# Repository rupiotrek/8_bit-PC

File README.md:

# 8_bit-PC

Project based on the project of [8 bit PC by Ben Eater](https://eater.net/8bit/ "8 bit by Ben Eater").  

# Version 1

Contains:
1. 3 board & schematic designs
2. Gerber files for production
3. BOM 

Board divided into 3 parts:

## Left

|Name of unit|Description|
| ------------ | ----------|
|**Clock**|Creats clock signal for the board. Can be used also as debugger - clock signal can be made by user |
|**Memory address (MAR)**|Choose from which address PC reads. In *Prog*  mode user can specify address to which instructions in RAM module will be written |
|**RAM**| Contains instructions for specified memory address. In *Prog* mode user can specify instruction for chosen in MAR module addres   |
|**Instruction register (IR)**| Decides which step of the program will be made next. It is sent to PC module. Also sends the address to read from  |
|**Control Word (CW)**| Operates whole PC. Also shows which flag is ON during working|

## Middle
|Name of unit|Description|
| ----- |-----|
|**Display module**|Shows current information on the bus   |
|**Sorting module**|Unit transports signals from left and right board to specified unit|

## Right
|Name of unit|Description|
|-----|-----|
|**Program counter (PC)**|Makes steps for the PC. Can also change them because of *jump* function    |
|**Power**| Main power unit. Contains overvoltage and reverse polarity protection |
|**A register**|Register that can read from and write informations for the bus. Contains information on which computer is working recently |
|**Arithmetic Logic Unit (ALU)**| Mathematical unit. Operates on variables from A and B registers. Module can add and substruct them   |
|**B register**|Register that can read informations from the bus. Contains information on which computer is working recently  |
|**Output register**| Show the variable on 4 display LED. Unit has two modes: non-neagtive and negative  |

# Links

This materials were really helpful during creation:

+ [Tutorial how to build the 8 bit PC](https://www.youtube.com/watch?v=HyznrdDSSGM&list=PLowKtXNTBypGqImE405J2565dvjafglHU)
+ [Ben Eater project site](https://eater.net/8bit/ )
+ [Helpful list of 74ls series ](https://www.futurlec.com/IC74LS00Series.shtml)

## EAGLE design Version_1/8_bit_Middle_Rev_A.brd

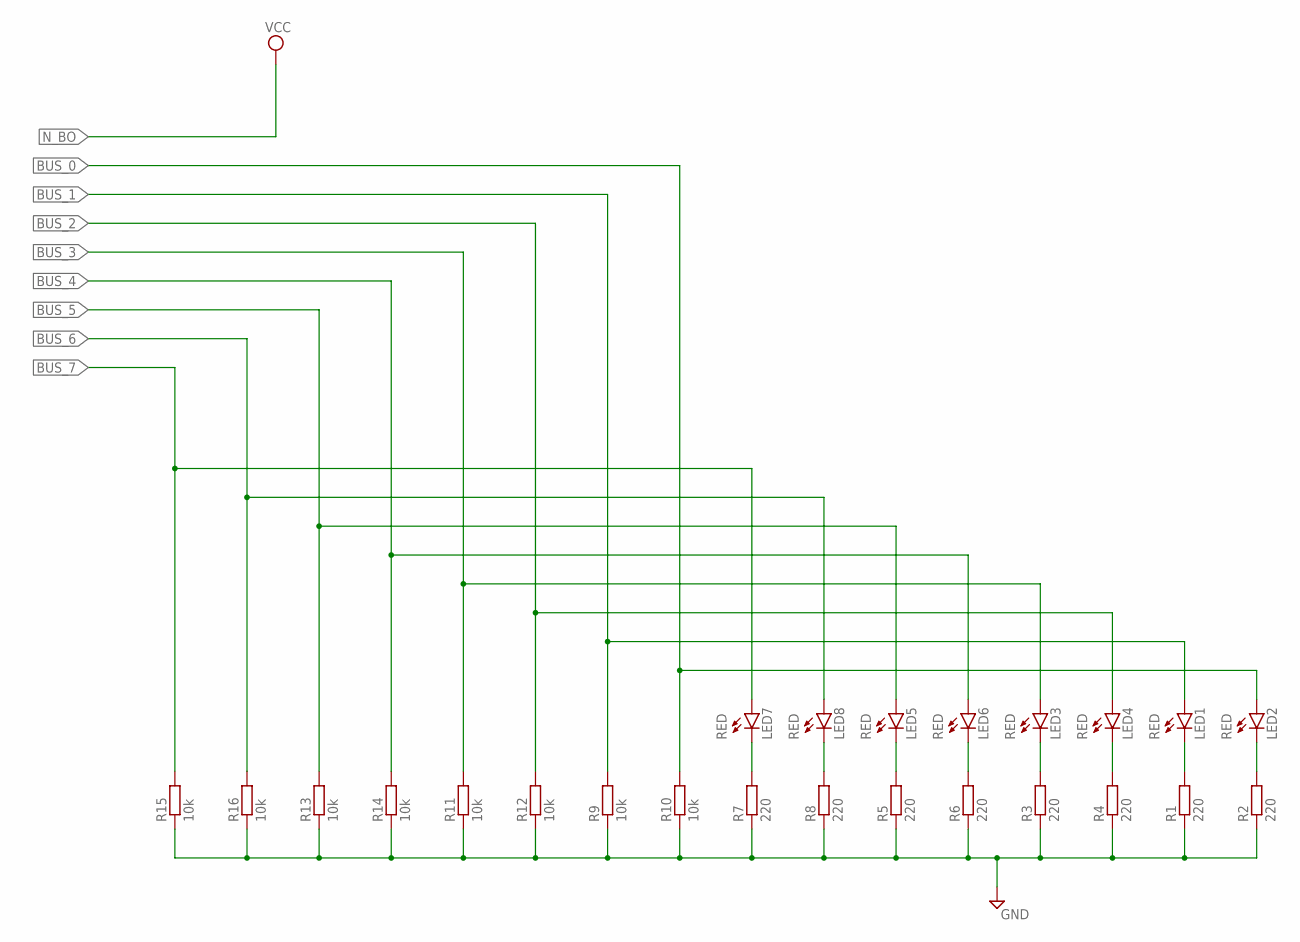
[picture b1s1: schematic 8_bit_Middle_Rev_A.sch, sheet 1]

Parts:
LED1, LED2, LED3, LED4, LED5, LED6, LED7, LED8: RED; LED5MM
R1, R2, R3, R4, R5, R6, R7, R8: 220; 0207/10
R9, R10, R11, R12, R13, R14, R15, R16: 10k; 0207/10

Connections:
BUS_0: LED2.A, R10.2; also elsewhere on the board
BUS_1: LED1.A, R9.2; also elsewhere on the board
BUS_2: LED4.A, R12.2; also elsewhere on the board
BUS_3: LED3.A, R11.2; also elsewhere on the board
BUS_4: LED6.A, R14.2; also elsewhere on the board
BUS_5: LED5.A, R13.2; also elsewhere on the board
BUS_6: LED8.A, R16.2; also elsewhere on the board
BUS_7: LED7.A, R15.2; also elsewhere on the board
GND: R1.1, R2.1, R3.1, R4.1, R5.1, R6.1, R7.1, R8.1, R9.1, R10.1, R11.1, R12.1, R13.1, R14.1, R15.1, R16.1; also elsewhere on the board
GND1: LED1.K (C), R1.2
GND2: LED2.K (C), R2.2
GND3: LED3.K (C), R3.2
GND5: LED4.K (C), R4.2
GND7: LED5.K (C), R5.2
GND8: LED6.K (C), R6.2
GND9: LED7.K (C), R7.2
GND10: LED8.K (C), R8.2

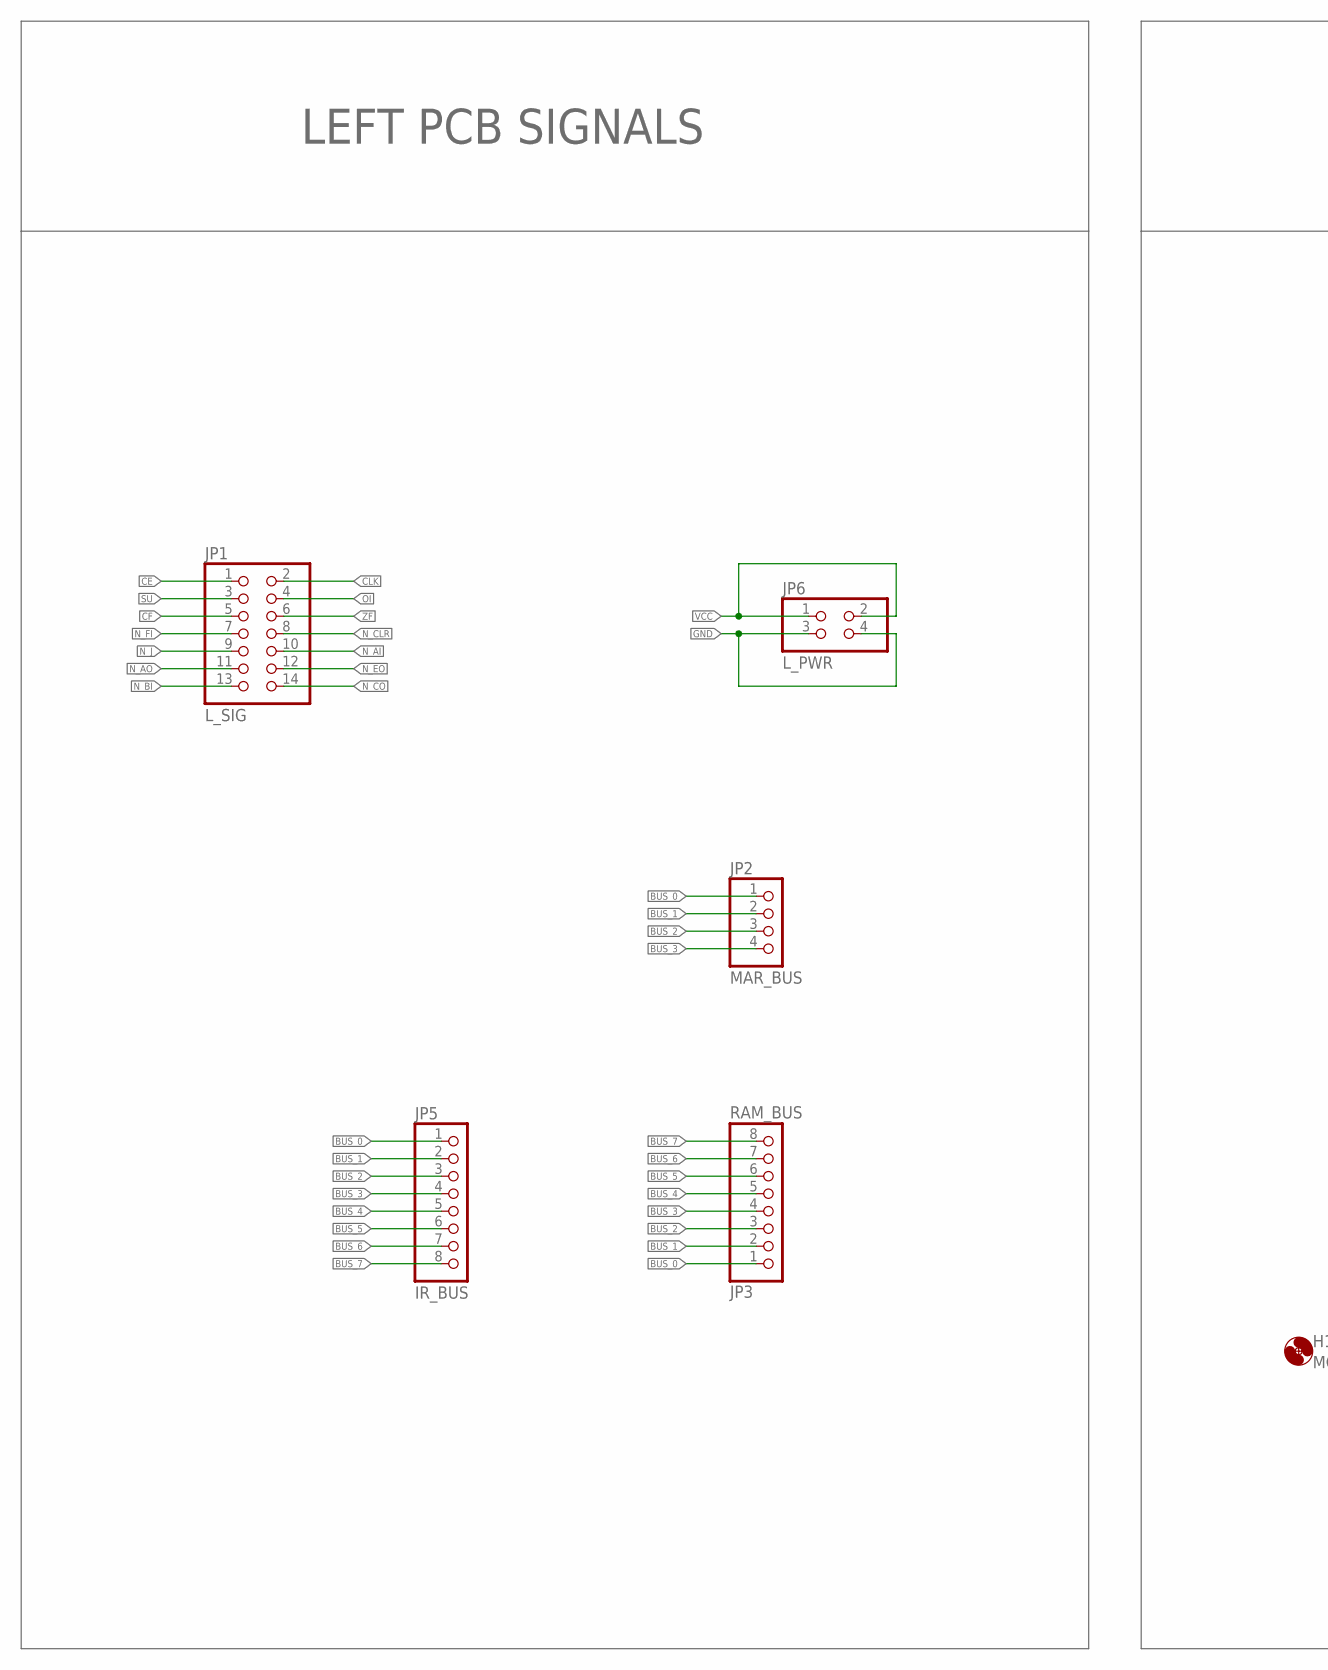
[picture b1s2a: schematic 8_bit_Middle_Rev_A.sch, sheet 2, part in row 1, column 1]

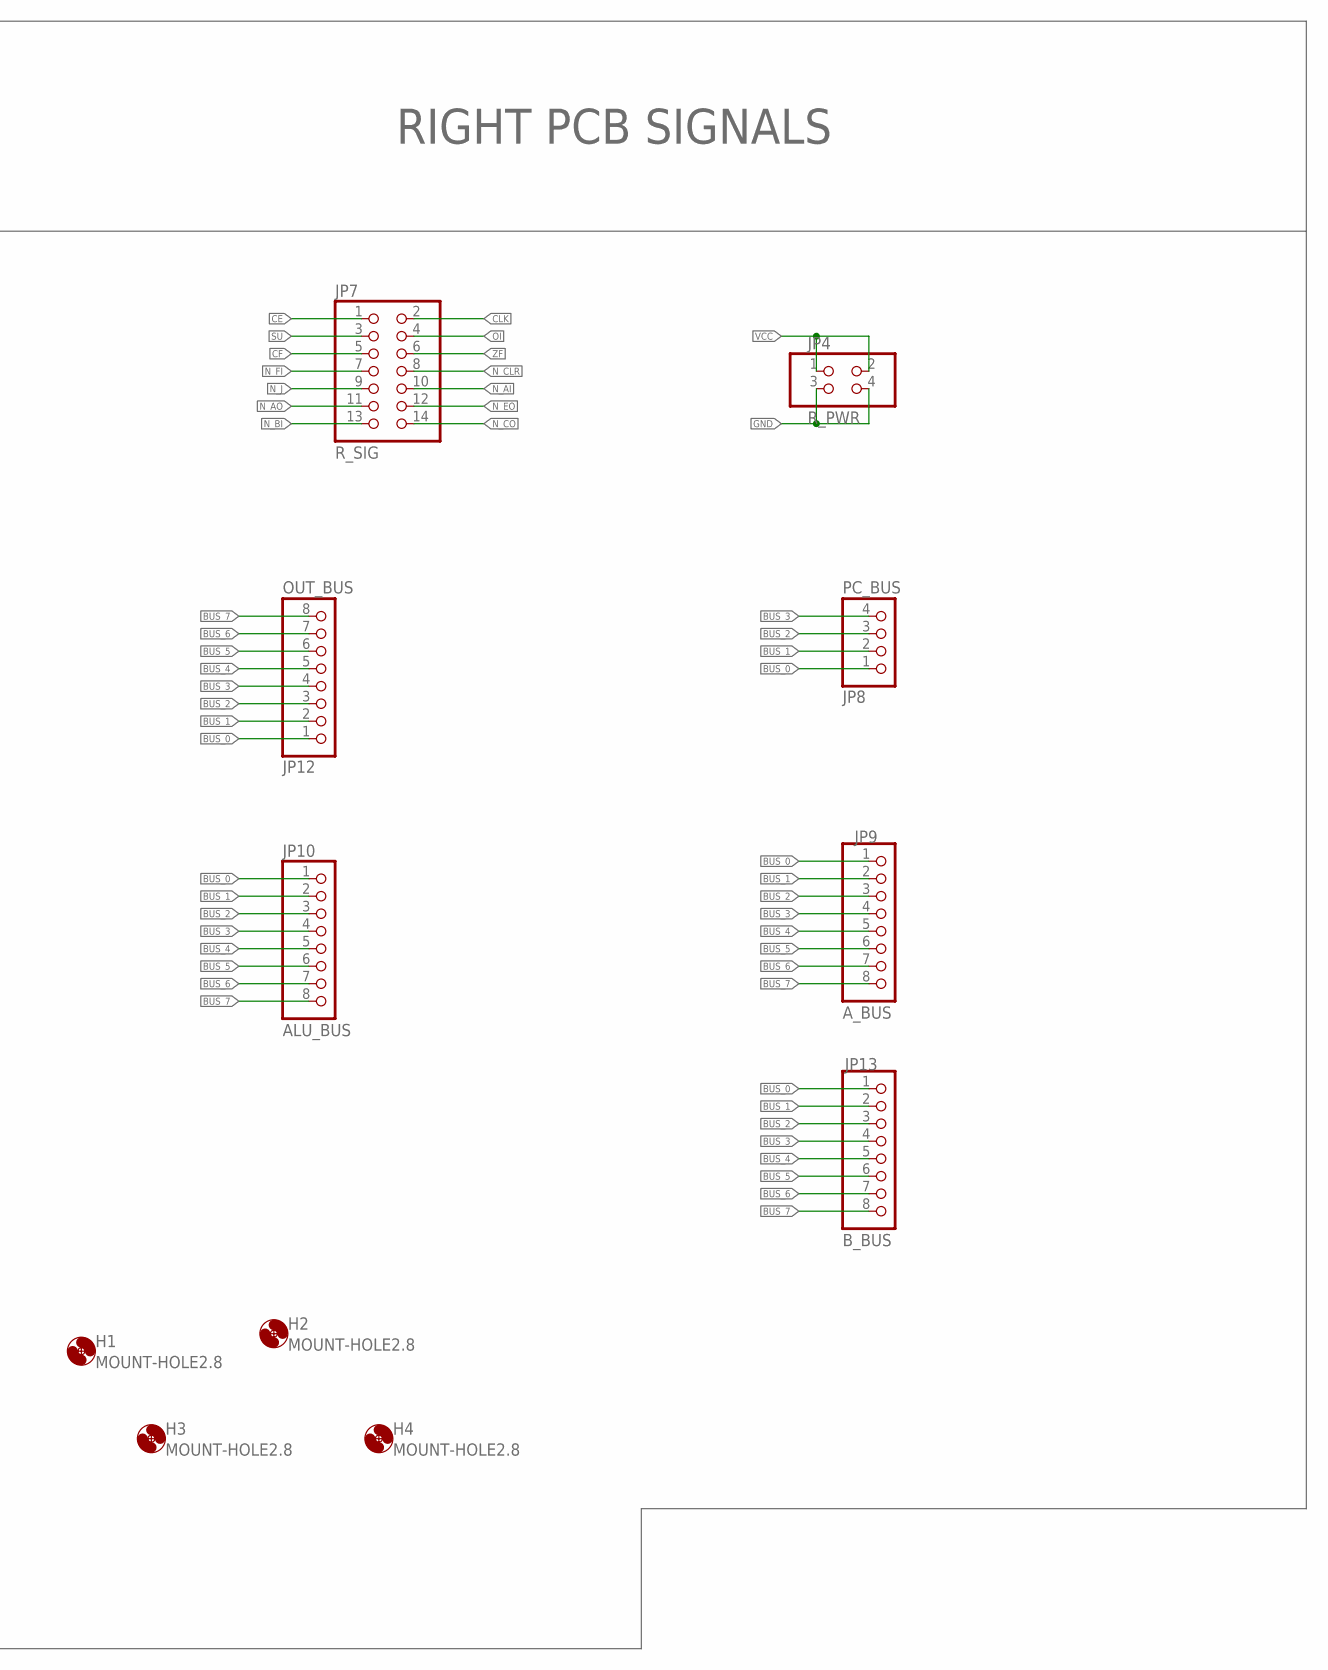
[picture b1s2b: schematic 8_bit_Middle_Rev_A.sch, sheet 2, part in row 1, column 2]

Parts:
H1, H2, H3, H4: MOUNT-HOLE2.8; 2,8
JP1: L_SIG; 2X07
JP2: MAR_BUS; 1X04
JP3: RAM_BUS; 1X08
JP4: R_PWR; 2X02
JP5: IR_BUS; 1X08
JP6: L_PWR; 2X02
JP7: R_SIG; 2X07
JP8: PC_BUS; 1X04
JP9: A_BUS; 1X08
JP10: ALU_BUS; 1X08
JP12: OUT_BUS; 1X08
JP13: B_BUS; 1X08

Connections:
BUS_0: JP2.1, JP3.1, JP5.1, JP8.1, JP9.1, JP10.1, JP12.1, JP13.1; also elsewhere on the board
BUS_1: JP2.2, JP3.2, JP5.2, JP8.2, JP9.2, JP10.2, JP12.2, JP13.2; also elsewhere on the board
BUS_2: JP2.3, JP3.3, JP5.3, JP8.3, JP9.3, JP10.3, JP12.3, JP13.3; also elsewhere on the board
BUS_3: JP2.4, JP3.4, JP5.4, JP8.4, JP9.4, JP10.4, JP12.4, JP13.4; also elsewhere on the board
BUS_4: JP3.5, JP5.5, JP9.5, JP10.5, JP12.5, JP13.5; also elsewhere on the board
BUS_5: JP3.6, JP5.6, JP9.6, JP10.6, JP12.6, JP13.6; also elsewhere on the board
BUS_6: JP3.7, JP5.7, JP9.7, JP10.7, JP12.7, JP13.7; also elsewhere on the board
BUS_7: JP3.8, JP5.8, JP9.8, JP10.8, JP12.8, JP13.8; also elsewhere on the board
CE: JP1.1, JP7.1
CF: JP1.5, JP7.5
CLK: JP1.2, JP7.2
GND: JP4.3, JP4.4, JP6.3, JP6.4; also elsewhere on the board
N_AI: JP1.10, JP7.10
N_AO: JP1.11, JP7.11
N_BI: JP1.13, JP7.13
N_CLR: JP1.8, JP7.8
N_CO: JP1.14, JP7.14
N_EO: JP1.12, JP7.12
N_FI: JP1.7, JP7.7
N_J: JP1.9, JP7.9
OI: JP1.4, JP7.4
SU: JP1.3, JP7.3
VCC: JP4.1, JP4.2, JP6.1, JP6.2
ZF: JP1.6, JP7.6

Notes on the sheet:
LEFT PCB SIGNALS
RIGHT PCB SIGNALS

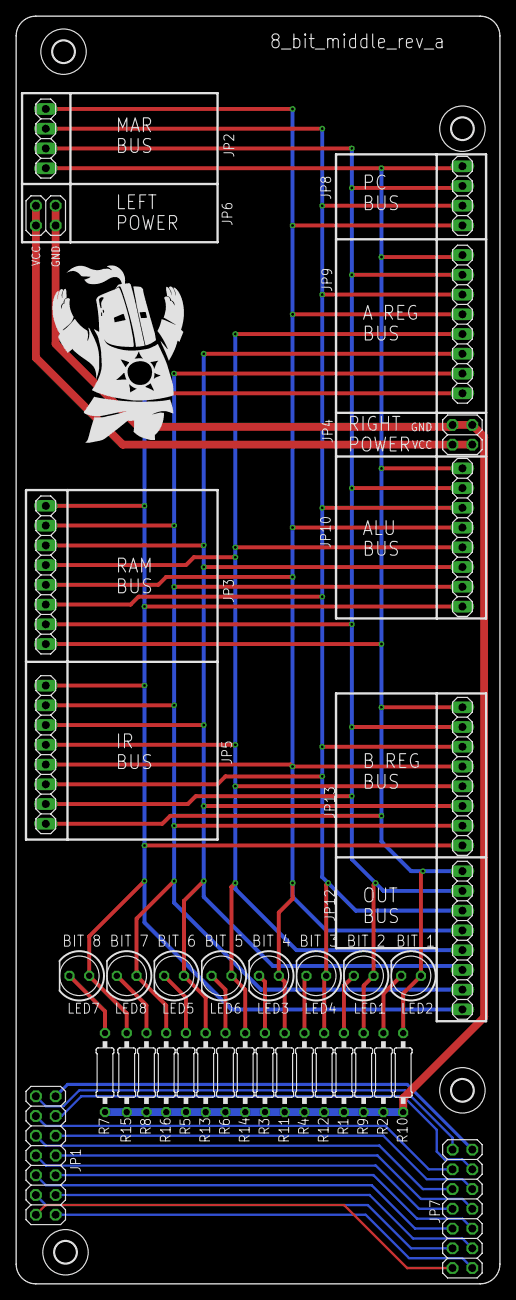
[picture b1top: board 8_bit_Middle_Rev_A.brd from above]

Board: 2 copper layers, 62.2 x 163.1 mm, 42 parts (1 on the bottom side), 32 nets.

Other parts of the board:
U$1: SOLAIRE
U$2: MUELLTONNE

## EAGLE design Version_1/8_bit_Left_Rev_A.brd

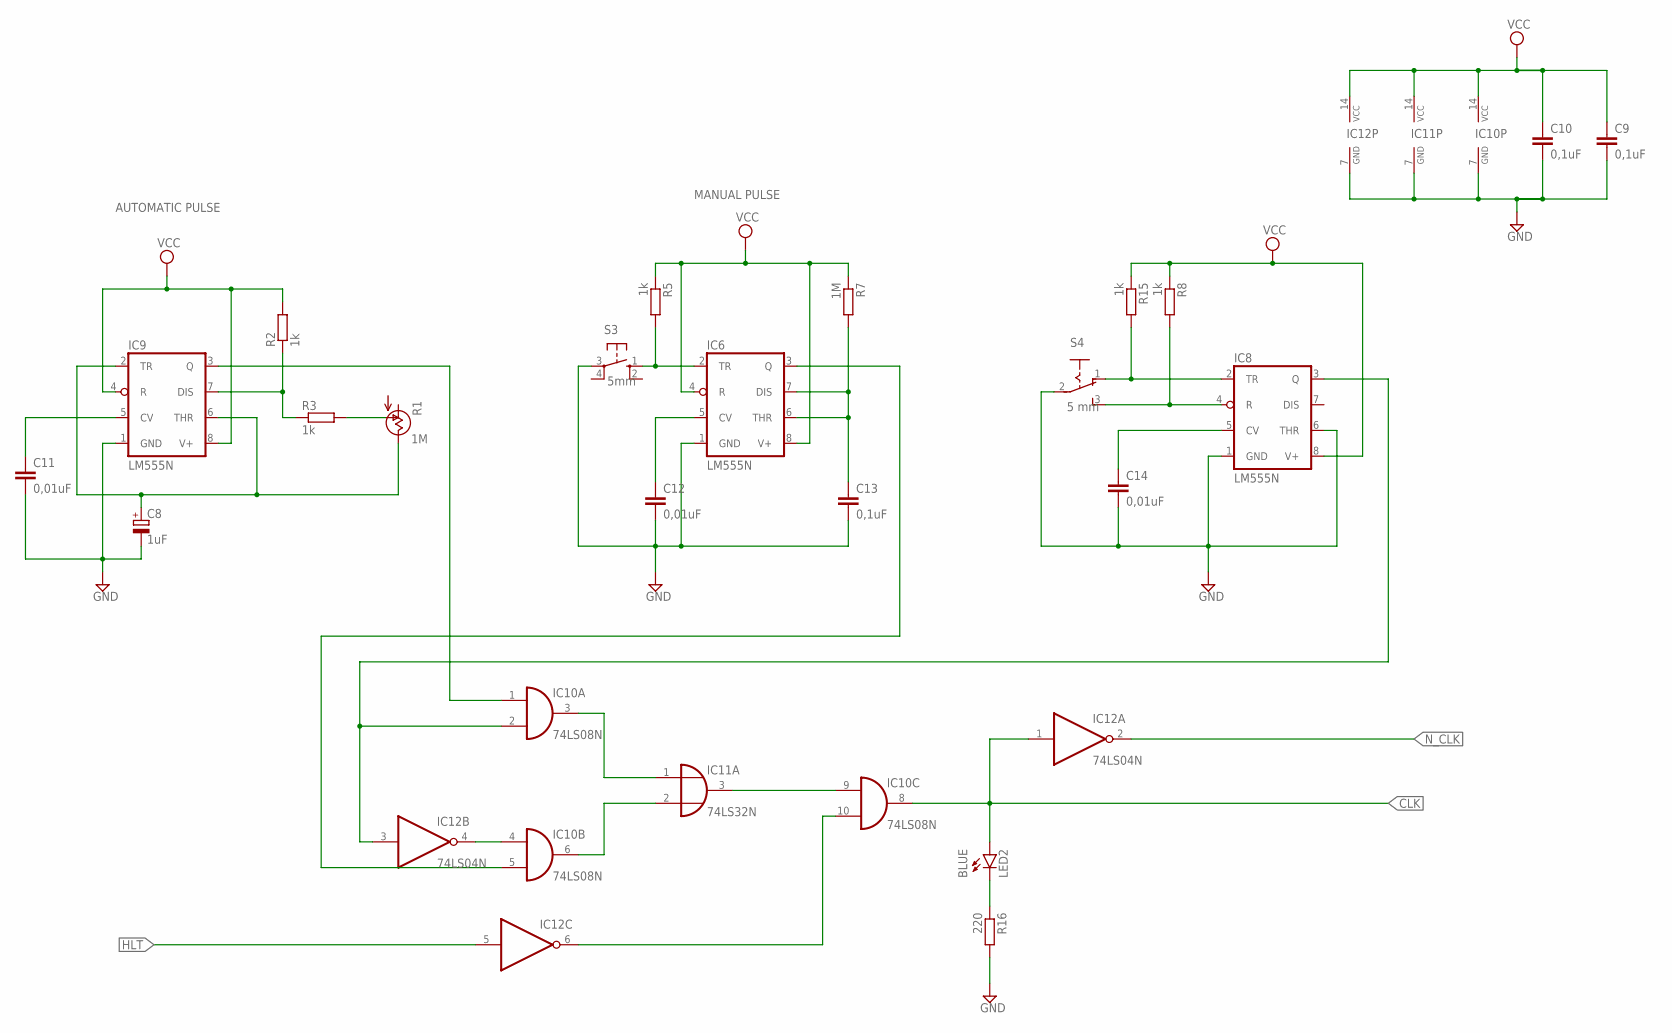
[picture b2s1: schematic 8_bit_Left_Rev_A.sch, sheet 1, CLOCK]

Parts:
C8: 1uF; E2-5
C9, C10, C13: 0,1uF; C025-030X050
C11, C12, C14: 0,01uF; C025-030X050
IC6, IC8, IC9: LM555N; DIL08
IC10: 74LS08N; DIL14
IC11: 74LS32N; DIL14
IC12: 74LS04N; DIL14
LED2: BLUE; LED5MM
R1: 1M; S64W
R2, R3, R5, R8, R15: 1k; 0207/10
R7: 1M; 0207/10
R16: 220; 0207/10
S3: 5mm; B3F-10XX
S4: 5 mm; 255SB

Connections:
CLK: IC10.8 (O), IC12.1 (I), LED2.A; also elsewhere on the board
GND: C8.-, C9.2, C10.2, C11.2, C12.2, C13.2, C14.2, IC6.1 (GND), IC8.1 (GND), IC8.6 (THR), IC9.1 (GND), IC10.7 (GND), IC11.7 (GND), IC12.7 (GND), R16.2, S3.3, S4.2; also elsewhere on the board
HLT: IC12.5 (I); also elsewhere on the board
unnamed: IC9.7 (DIS), R2.1, R3.1
unnamed: C8.+, IC9.2 (TR), IC9.6 (THR), R1.E (VSS)
unnamed: C11.1, IC9.5 (CV)
unnamed: C12.1, IC6.5 (CV)
unnamed: C13.1, IC6.6 (THR), IC6.7 (DIS), R7.2
unnamed: IC6.2 (TR), R5.2, S3.1 (S)
unnamed: IC8.4 (R), R8.2, S4.3 (S)
unnamed: IC8.2 (TR), R15.2, S4.1 (O)
unnamed: C14.1, IC8.5 (CV)
unnamed: IC9.3 (Q), IC10.1 (I0)
unnamed: IC6.3 (Q), IC10.5 (I1)
unnamed: IC10.4 (I0), IC12.4 (O)
unnamed: IC8.3 (Q), IC10.2 (I1), IC12.3 (I)
unnamed: IC10.3 (O), IC11.1 (I0)
unnamed: IC10.6 (O), IC11.2 (I1)
unnamed: IC10.9 (I0), IC11.3 (O)
unnamed: IC10.10 (I1), IC12.6 (O)
unnamed: R1.S (OUT), R3.2
unnamed: LED2.K (C), R16.1
N_CLK: IC12.2 (O); also elsewhere on the board
VCC: C9.1, C10.1, IC6.4 (R), IC6.8 (V+), IC8.8 (V+), IC9.4 (R), IC9.8 (V+), IC10.14 (VCC), IC11.14 (VCC), IC12.14 (VCC), R2.2, R5.1, R7.1, R8.1, R15.1; also elsewhere on the board

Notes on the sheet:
MANUAL PULSE
AUTOMATIC PULSE

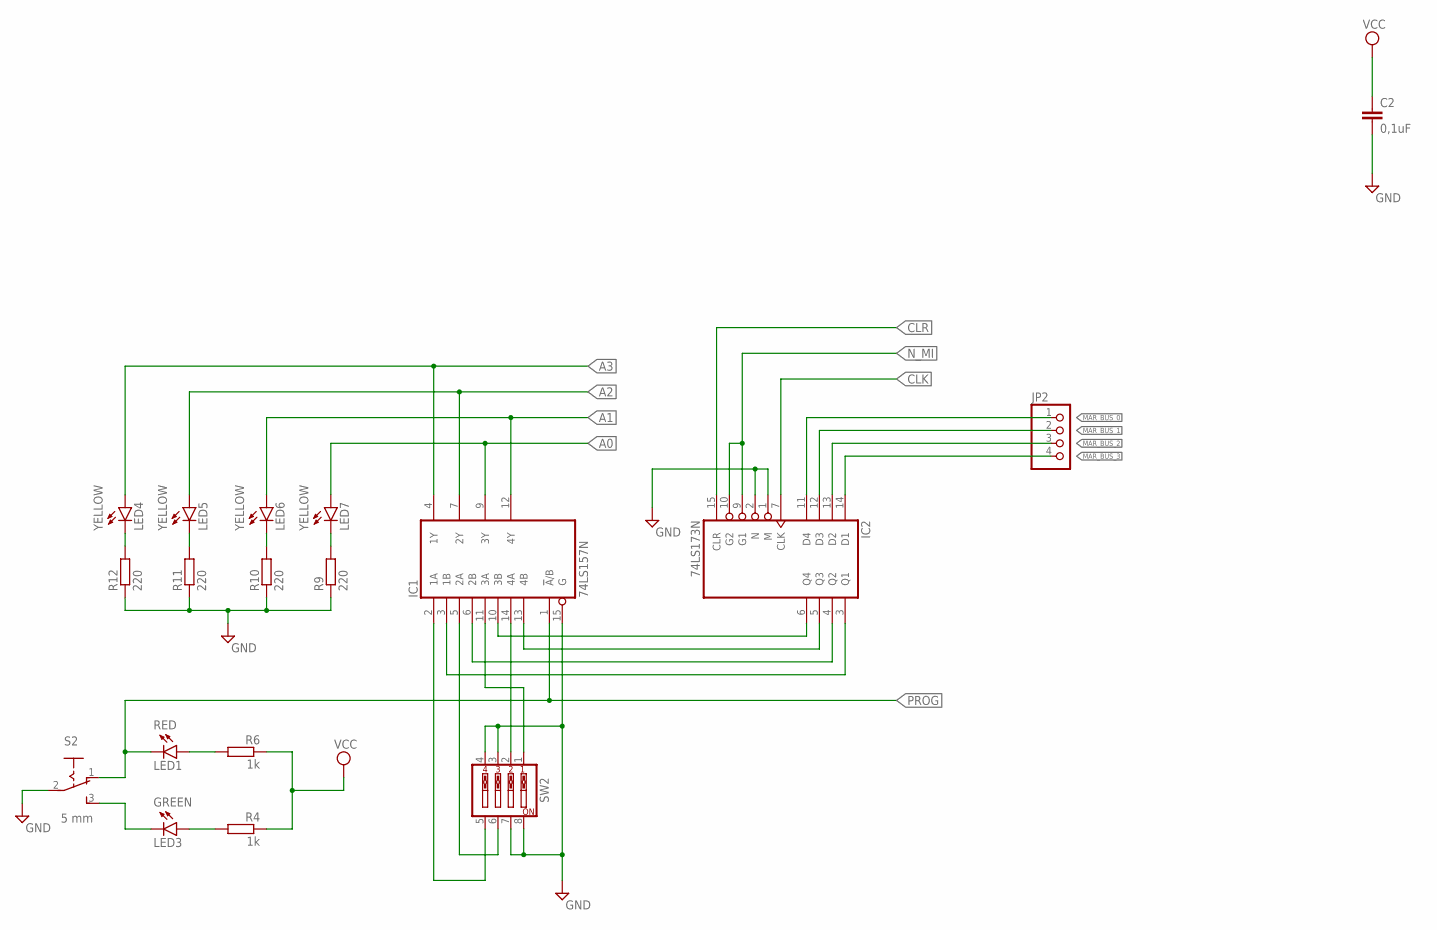
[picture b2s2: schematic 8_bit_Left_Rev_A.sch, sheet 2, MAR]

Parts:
C2: 0,1uF; C025-030X050
IC1: 74LS157N; DIL16
IC2: 74LS173N; DIL16
JP2: PINHD-1X4; 1X04
LED1: RED; LED5MM
LED3: GREEN; LED5MM
LED4, LED5, LED6, LED7: YELLOW; LED5MM
R4, R6: 1k; 0207/10
R9, R10, R11, R12: 220; 0207/10
S2: 5 mm; 255SB
SW2: EDG-04

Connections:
A0: IC1.9 (3Y), LED7.A; also elsewhere on the board
A1: IC1.12 (4Y), LED6.A; also elsewhere on the board
A2: IC1.7 (2Y), LED5.A; also elsewhere on the board
A3: IC1.4 (1Y), LED4.A; also elsewhere on the board
CLK: IC2.7 (CLK); also elsewhere on the board
CLR: IC2.15 (CLR); also elsewhere on the board
GND: C2.2, IC1.8 (GND), IC1.15 (G), IC2.1 (M), IC2.2 (N), IC2.8 (GND), R9.1, R10.1, R11.1, R12.1, S2.2, SW2.3, SW2.4, SW2.7, SW2.8; also elsewhere on the board
GND1: LED7.K (C), R9.2
GND2: LED6.K (C), R10.2
GND3: LED5.K (C), R11.2
GND4: LED4.K (C), R12.2
MAR_BUS_0: IC2.11 (D4), JP2.1
MAR_BUS_1: IC2.12 (D3), JP2.2
MAR_BUS_2: IC2.13 (D2), JP2.3
MAR_BUS_3: IC2.14 (D1), JP2.4
unnamed: LED1.A, R6.2
unnamed: LED3.A, R4.2
unnamed: LED3.K (C), S2.3 (S)
unnamed: IC1.14 (4A), SW2.2
unnamed: IC1.11 (3A), SW2.1
unnamed: IC1.10 (3B), IC2.6 (Q4)
unnamed: IC1.13 (4B), IC2.5 (Q3)
unnamed: IC1.6 (2B), IC2.4 (Q2)
unnamed: IC1.3 (1B), IC2.3 (Q1)
unnamed: IC1.5 (2A), SW2.6
unnamed: IC1.2 (1A), SW2.5
N_MI: IC2.9 (G1), IC2.10 (G2); also elsewhere on the board
PROG: IC1.1 (!A!/B), LED1.K (C), S2.1 (O); also elsewhere on the board
VCC: C2.1, IC1.16 (VCC), IC2.16 (VCC), R4.1, R6.1; also elsewhere on the board

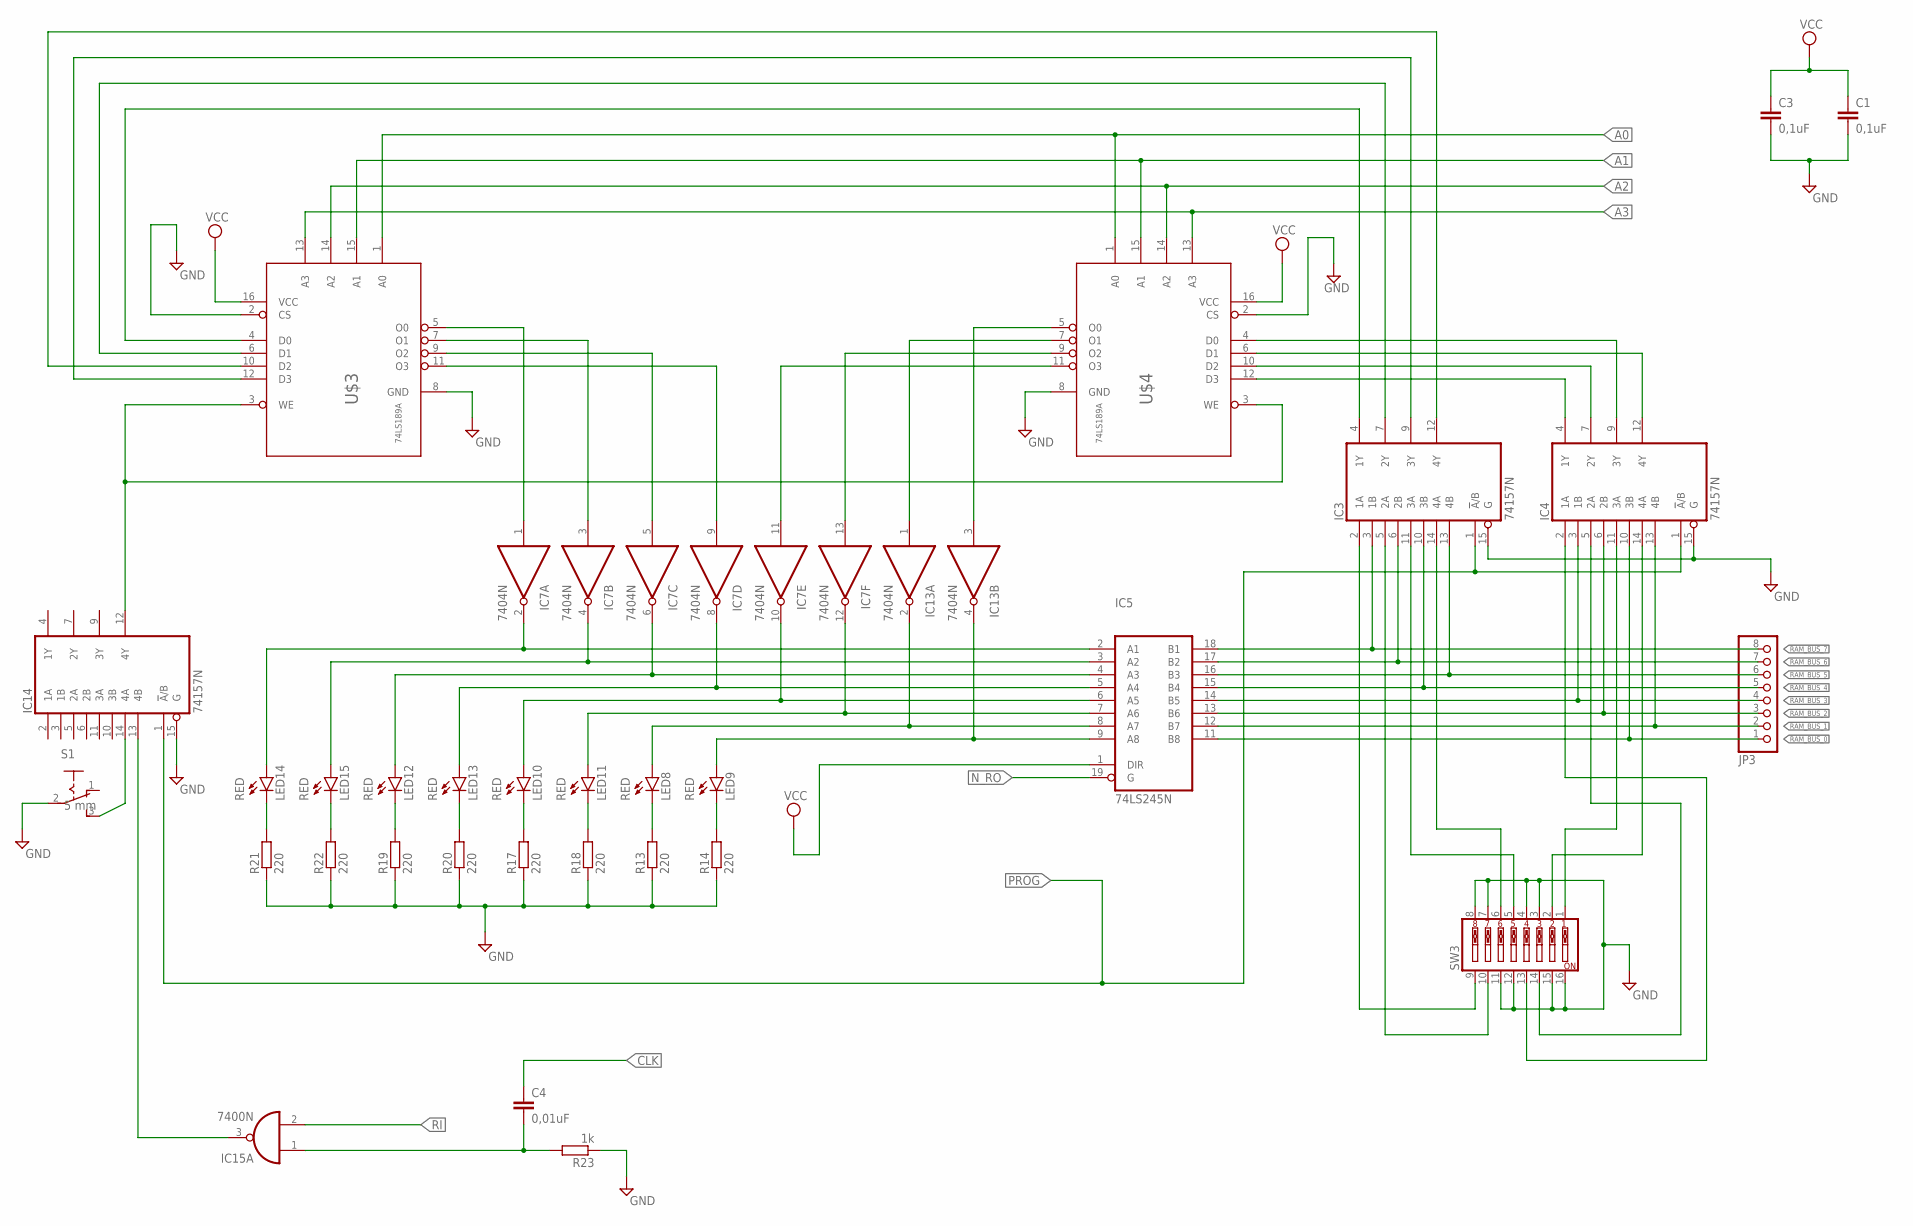
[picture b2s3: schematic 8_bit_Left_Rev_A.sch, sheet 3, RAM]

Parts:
C1, C3: 0,1uF; C025-030X050
C4: 0,01uF; C025-030X050
IC3, IC4, IC14: 74157N; DIL16
IC5: 74LS245N; DIL20
IC7, IC13: 7404N; DIL14
IC15: 7400N; DIL14
JP3: PINHD-1X8; 1X08
LED8, LED9, LED10, LED11, LED12, LED13, LED14, LED15: RED; LED5MM
R13, R14, R17, R18, R19, R20, R21, R22: 220; 0207/10
R23: 1k; 0207/10
S1: 5 mm; 255SB
SW3: EDG-08
U$3, U$4: 74LS189A; 74LS189

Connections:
A0: U$3.1 (A0), U$4.1 (A0); also elsewhere on the board
A1: U$3.15 (A1), U$4.15 (A1); also elsewhere on the board
A2: U$3.14 (A2), U$4.14 (A2); also elsewhere on the board
A3: U$3.13 (A3), U$4.13 (A3); also elsewhere on the board
CLK: C4.1; also elsewhere on the board
GND: C1.2, C3.2, IC3.8 (GND), IC3.15 (G), IC4.8 (GND), IC4.15 (G), IC5.10 (GND), IC7.7 (GND), IC13.7 (GND), IC14.8 (GND), IC14.15 (G), IC15.7 (GND), R13.1, R14.1, R17.1, R18.1, R19.1, R20.1, R21.1, R22.1, R23.1, S1.2, SW3.3, SW3.4, SW3.7, SW3.8, SW3.11, SW3.12, SW3.15, SW3.16, U$3.2 (CS), U$3.8 (GND), U$4.2 (CS), U$4.8 (GND); also elsewhere on the board
GND5: LED8.K (C), R13.2
GND6: LED9.K (C), R14.2
GND7: LED10.K (C), R17.2
GND8: LED11.K (C), R18.2
GND9: LED12.K (C), R19.2
GND10: LED13.K (C), R20.2
GND11: LED14.K (C), R21.2
GND12: LED15.K (C), R22.2
unnamed: IC3.4 (1Y), U$3.4 (D0)
unnamed: IC3.7 (2Y), U$3.6 (D1)
unnamed: IC3.9 (3Y), U$3.12 (D3)
unnamed: IC3.12 (4Y), U$3.10 (D2)
unnamed: IC14.12 (4Y), U$3.3 (WE), U$4.3 (WE)
unnamed: IC13.3 (I), U$4.5 (O0)
unnamed: IC13.1 (I), U$4.7 (O1)
unnamed: IC7.13 (I), U$4.9 (O2)
unnamed: IC7.11 (I), U$4.11 (O3)
unnamed: IC7.1 (I), U$3.5 (O0)
unnamed: IC7.3 (I), U$3.7 (O1)
unnamed: IC7.5 (I), U$3.9 (O2)
unnamed: IC7.9 (I), U$3.11 (O3)
unnamed: IC5.2 (A1), IC7.2 (O), LED14.A
unnamed: IC5.3 (A2), IC7.4 (O), LED15.A
unnamed: IC5.4 (A3), IC7.6 (O), LED12.A
unnamed: IC5.5 (A4), IC7.8 (O), LED13.A
unnamed: IC5.6 (A5), IC7.10 (O), LED10.A
unnamed: IC5.7 (A6), IC7.12 (O), LED11.A
unnamed: IC5.8 (A7), IC13.2 (O), LED8.A
unnamed: IC5.9 (A8), IC13.4 (O), LED9.A
unnamed: IC14.14 (4A), S1.3 (S)
unnamed: IC14.13 (4B), IC15.3 (O)
unnamed: C4.2, IC15.1 (I0), R23.2
unnamed: IC3.2 (1A), SW3.9
unnamed: IC3.5 (2A), SW3.10
unnamed: IC3.11 (3A), SW3.5
unnamed: IC3.14 (4A), SW3.6
unnamed: IC4.14 (4A), SW3.2
unnamed: IC4.5 (2A), SW3.14
unnamed: IC4.11 (3A), SW3.1
unnamed: IC4.2 (1A), SW3.13
unnamed: IC4.9 (3Y), U$4.4 (D0)
unnamed: IC4.4 (1Y), U$4.12 (D3)
unnamed: IC4.7 (2Y), U$4.10 (D2)
unnamed: IC4.12 (4Y), U$4.6 (D1)
N_RO: IC5.19 (G); also elsewhere on the board
PROG: IC3.1 (!A!/B), IC4.1 (!A!/B), IC14.1 (!A!/B); also elsewhere on the board
RAM_BUS_0: IC4.10 (3B), IC5.11 (B8), JP3.1
RAM_BUS_1: IC4.13 (4B), IC5.12 (B7), JP3.2
RAM_BUS_2: IC4.6 (2B), IC5.13 (B6), JP3.3
RAM_BUS_3: IC4.3 (1B), IC5.14 (B5), JP3.4
RAM_BUS_4: IC3.10 (3B), IC5.15 (B4), JP3.5
RAM_BUS_5: IC3.13 (4B), IC5.16 (B3), JP3.6
RAM_BUS_6: IC3.6 (2B), IC5.17 (B2), JP3.7
RAM_BUS_7: IC3.3 (1B), IC5.18 (B1), JP3.8
RI: IC15.2 (I1); also elsewhere on the board
VCC: C1.1, C3.1, IC3.16 (VCC), IC4.16 (VCC), IC5.1 (DIR), IC5.20 (VCC), IC7.14 (VCC), IC13.14 (VCC), IC14.16 (VCC), IC15.14 (VCC), U$3.16 (VCC), U$4.16 (VCC); also elsewhere on the board

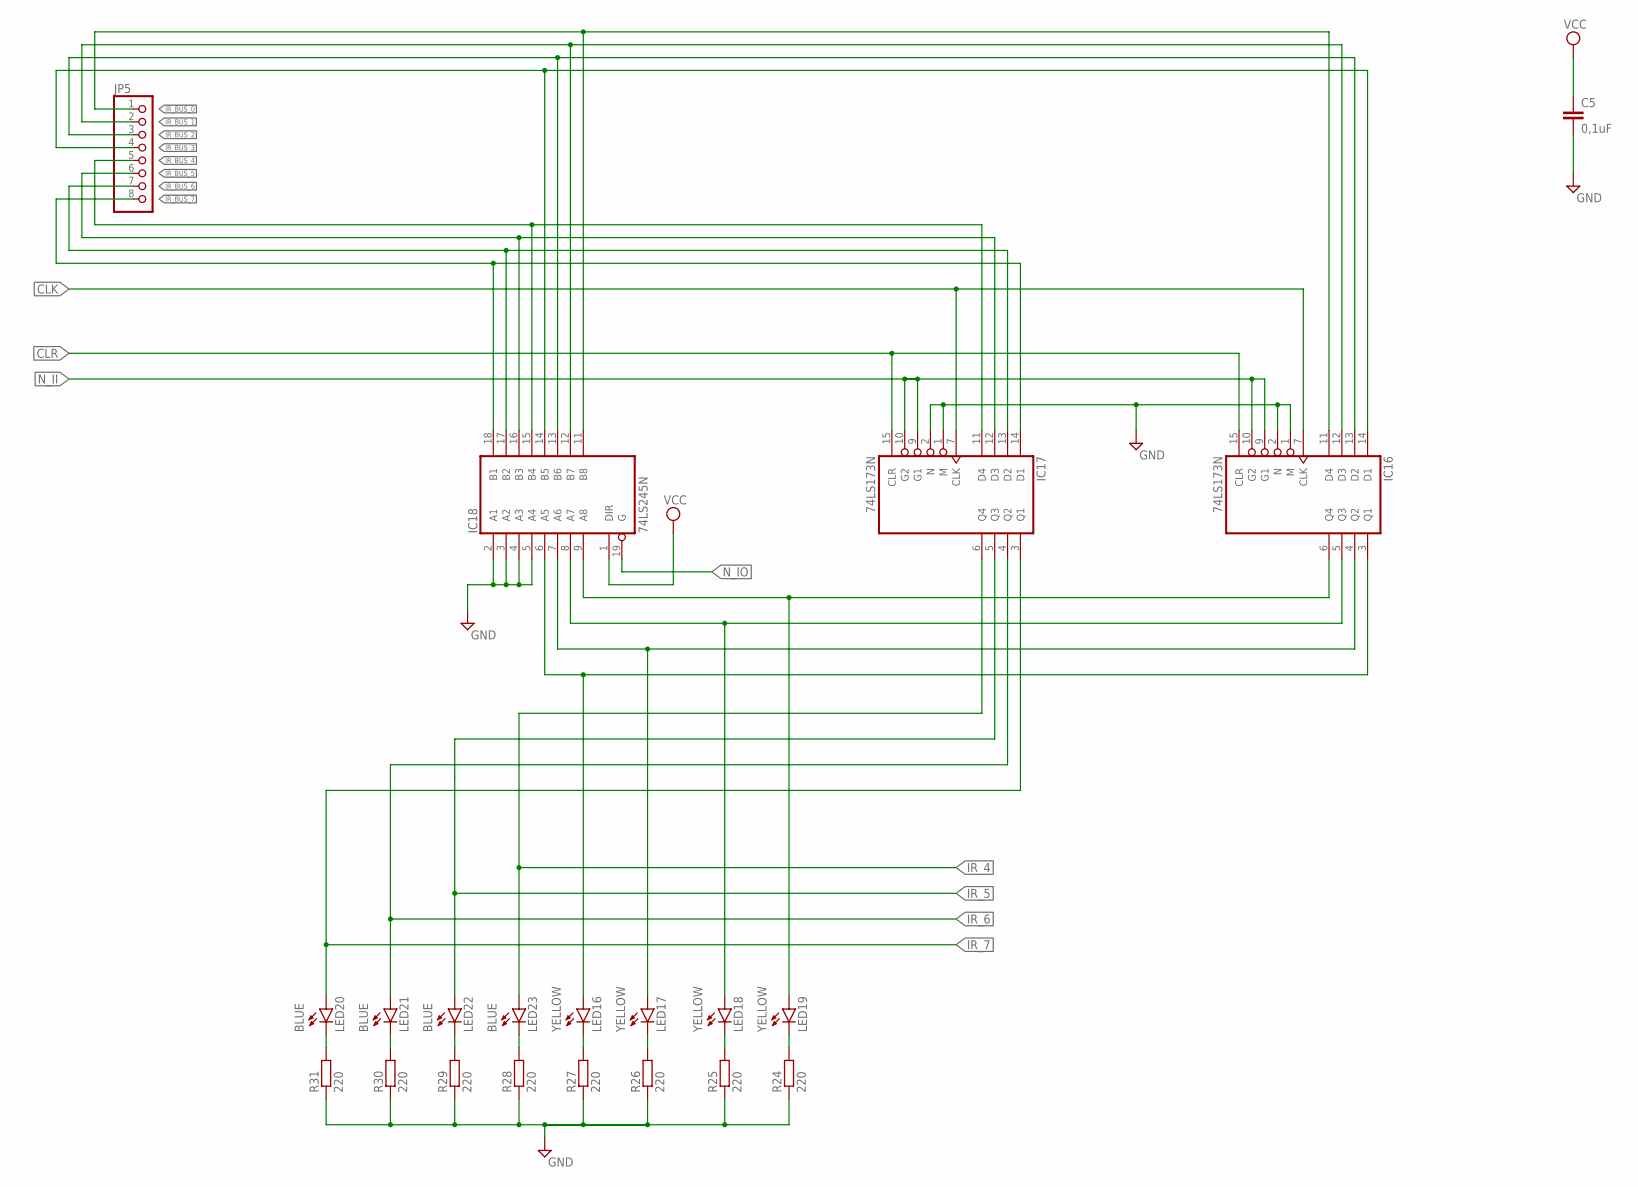
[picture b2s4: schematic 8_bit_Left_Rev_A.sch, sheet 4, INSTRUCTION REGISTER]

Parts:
C5: 0,1uF; C025-030X050
IC16, IC17: 74LS173N; DIL16
IC18: 74LS245N; DIL20
JP5: PINHD-1X8; 1X08
LED16, LED17, LED18, LED19: YELLOW; LED5MM
LED20, LED21, LED22, LED23: BLUE; LED5MM
R24, R25, R26, R27, R28, R29, R30, R31: 220; 0207/10

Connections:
CLK: IC16.7 (CLK), IC17.7 (CLK); also elsewhere on the board
CLR: IC16.15 (CLR), IC17.15 (CLR); also elsewhere on the board
GND: C5.2, IC16.1 (M), IC16.2 (N), IC16.8 (GND), IC17.1 (M), IC17.2 (N), IC17.8 (GND), IC18.2 (A1), IC18.3 (A2), IC18.4 (A3), IC18.5 (A4), IC18.10 (GND), R24.1, R25.1, R26.1, R27.1, R28.1, R29.1, R30.1, R31.1; also elsewhere on the board
GND15: LED19.K (C), R24.2
GND16: LED18.K (C), R25.2
GND17: LED17.K (C), R26.2
GND18: LED16.K (C), R27.2
GND19: LED23.K (C), R28.2
GND20: LED22.K (C), R29.2
GND21: LED21.K (C), R30.2
GND22: LED20.K (C), R31.2
IR_4: IC17.6 (Q4), LED23.A; also elsewhere on the board
IR_5: IC17.5 (Q3), LED22.A; also elsewhere on the board
IR_6: IC17.4 (Q2), LED21.A; also elsewhere on the board
IR_7: IC17.3 (Q1), LED20.A; also elsewhere on the board
IR_BUS_0: IC16.11 (D4), IC18.11 (B8), JP5.1
IR_BUS_1: IC16.12 (D3), IC18.12 (B7), JP5.2
IR_BUS_2: IC16.13 (D2), IC18.13 (B6), JP5.3
IR_BUS_3: IC16.14 (D1), IC18.14 (B5), JP5.4
IR_BUS_4: IC17.11 (D4), IC18.15 (B4), JP5.5
IR_BUS_5: IC17.12 (D3), IC18.16 (B3), JP5.6
IR_BUS_6: IC17.13 (D2), IC18.17 (B2), JP5.7
IR_BUS_7: IC17.14 (D1), IC18.18 (B1), JP5.8
unnamed: IC16.6 (Q4), IC18.9 (A8), LED19.A
unnamed: IC16.5 (Q3), IC18.8 (A7), LED18.A
unnamed: IC16.4 (Q2), IC18.7 (A6), LED17.A
unnamed: IC16.3 (Q1), IC18.6 (A5), LED16.A
N_II: IC16.9 (G1), IC16.10 (G2), IC17.9 (G1), IC17.10 (G2); also elsewhere on the board
N_IO: IC18.19 (G); also elsewhere on the board
VCC: C5.1, IC16.16 (VCC), IC17.16 (VCC), IC18.1 (DIR), IC18.20 (VCC); also elsewhere on the board
